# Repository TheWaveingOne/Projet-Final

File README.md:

# Projet-Final
 Projet synthèse pour mon DEC

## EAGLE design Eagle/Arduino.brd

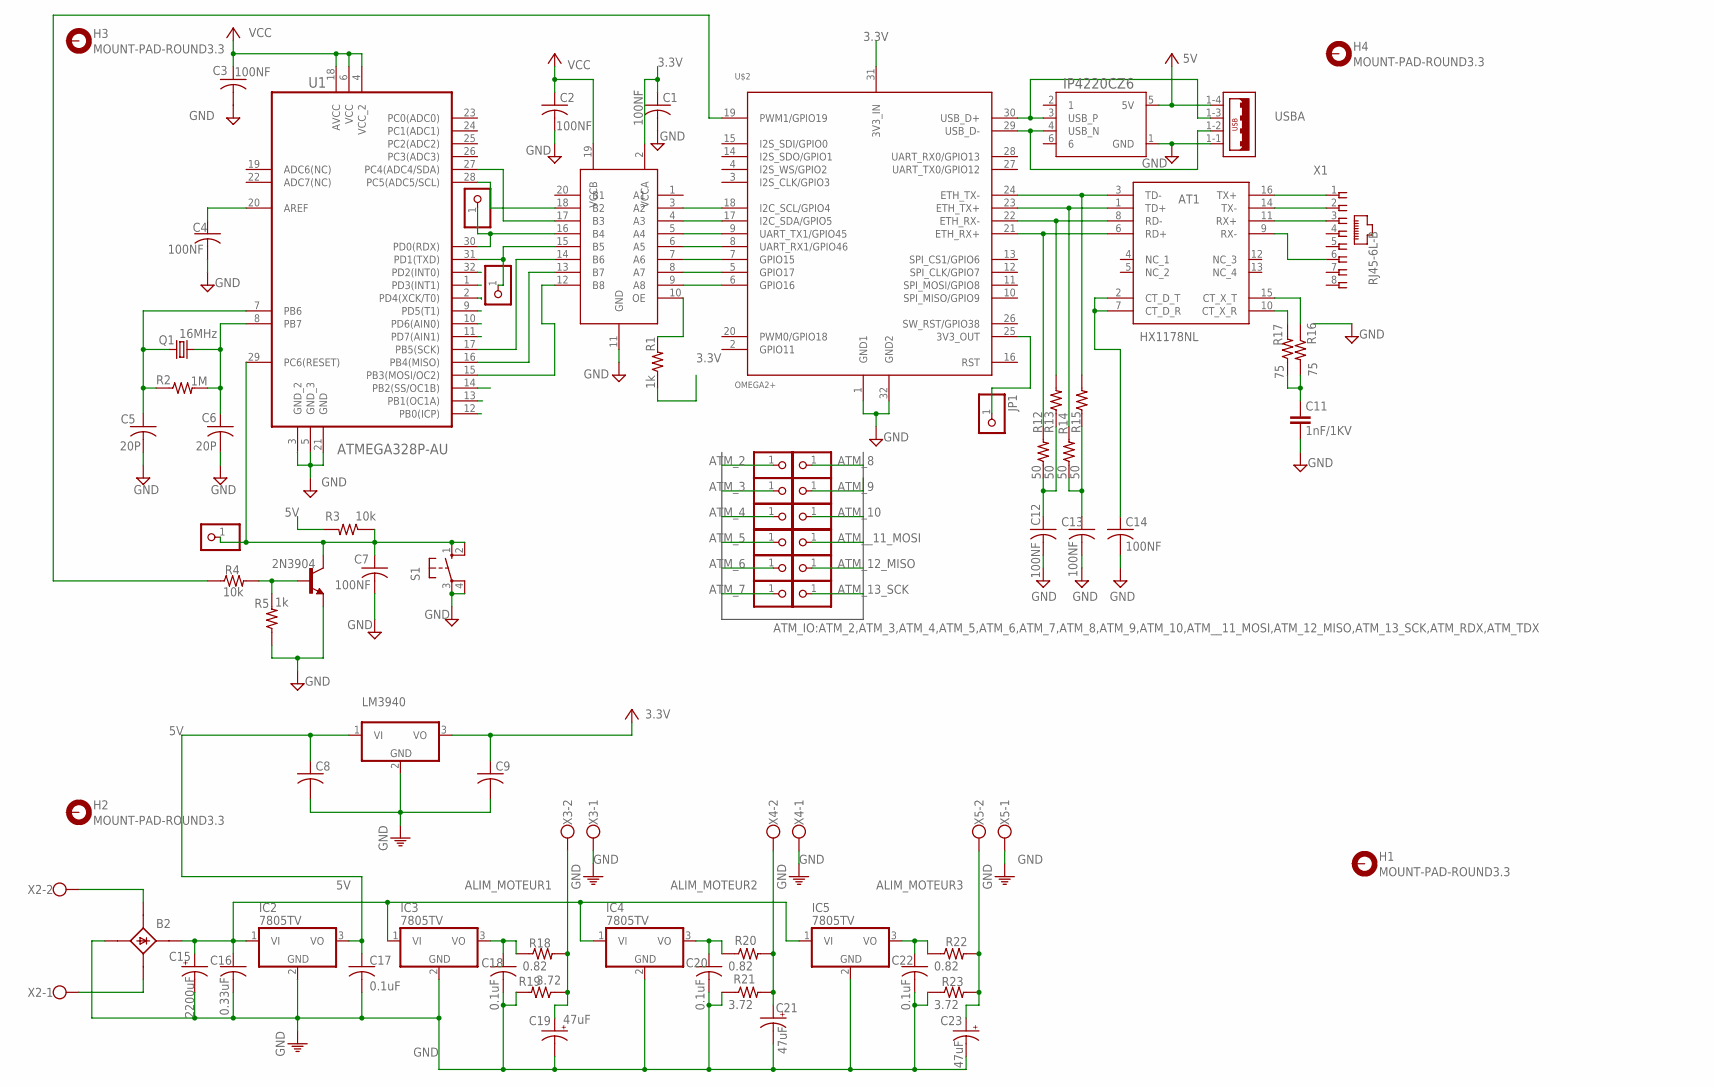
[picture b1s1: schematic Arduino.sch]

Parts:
AT1: HX1178NL; SOP254P1283X647-16N
B2: B25A-
C1, C2, C3, C4, C7, C12, C13, C14: 100NF; C0603K
C5, C6: 20P; C0603K
C8, C9: CENPC1206K; C1206K
C11: 1nF/1KV; XC10B6
C15: 2200uF; SANYO-OSCON_B'
C16: 0.33uF; C0603K
C17, C18, C20, C22: 0.1uF; C0603K
C19, C21, C23: 47uF; SANYO-OSCON_B'
FRAME1: CARTOUCHE_TGÉ; CARTOUCHE
H1, H2, H3, H4: MOUNT-PAD-ROUND3.3; 3,3-PAD
IC2, IC3, IC4, IC5: 7805TV; TO220V
IP4220CZ6: IP4220CZ6,125DIODE_SOT457_1P7X3P1-M; DIODE_SOT457_1P7X3P1-M
JP1, JP2, JP3, JP4, JP5, JP6, JP7, JP8, JP9, JP10, JP11, JP12, JP13, JP14, JP15, JP16: PINHD-1X1; 1X01
LM3940: 7824TV; TO220V
Q1: 16MHz; HC49/S
R1: 1k; M1206
R2: 1M; M1206
R3, R4: 10k; M1206
R5: 1k; M3216
R12, R13, R14, R15: 50; M1206
R16, R17: 75; M1206
R18, R20, R22: 0.82; 0309/10
R19, R21, R23: 3.72; 0309/10
S1: 10-XX; B3F-10XX
U1: ATMEGA328P-AU; QFP80P900X900X120-32N
U$1: TXS0108E; TSSOP20
U$2: OMEGA2+; OMEGA2_PADS
USB: USB_2P85-32003-00X-1; USB2
VERIFIER_TYPE: 2N3904; TO92
X1: RJ45-6L-B; RJ45-NO-SHIELD
X2, X3, X4, X5: W237-102

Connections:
3.3V: C1.1, C9.1, LM3940.3 (VO), R1.1, U$1.2 (VCCA), U$2.31 (3V3_IN)
5V: C2.1, C3.1, C8.1, C17.1, IC2.3 (VO), IP4220CZ6.5 (5V), LM3940.1 (VI), R3.2, U1.4 (VCC_2), U1.6 (VCC), U1.18 (AVCC), U$1.19 (VCCB), USB.1-4 (4)
ALIM_MOTEUR1: C19.+, R18.2, R19.1, X3.2
ALIM_MOTEUR2: C21.+, R20.2, R21.2, X4.2
ALIM_MOTEUR3: C23.+, R22.2, R23.2, X5.2
ATM_2: JP3.1, U1.32 (PD2(INT0))
ATM_3: JP4.1, U1.1 (PD3(INT1))
ATM_4: JP7.1, U1.2 (PD4(XCK/T0))
ATM_5: JP8.1, U1.9 (PD5(T1))
ATM_6: JP9.1, U1.10 (PD6(AIN0))
ATM_7: JP10.1, U1.11 (PD7(AIN1))
ATM_8: JP11.1, U1.12 (PB0(ICP))
ATM_9: JP12.1, U1.13 (PB1(OC1A))
ATM_10: JP13.1, U1.14 (PB2(SS/OC1B))
ATM_12_MISO: JP15.1, U1.16 (PB4(MISO)), U$1.13 (B7)
ATM_13_SCK: JP16.1, U1.17 (PB5(SCK)), U$1.14 (B6)
ATM_RDX: JP5.1, U1.30 (PD0(RDX)), U$1.16 (B4)
ATM_SCI: U1.28 (PC5(ADC5/SCL)), U$1.18 (B2)
ATM_SDA: U1.27 (PC4(ADC4/SDA)), U$1.17 (B3)
ATM_TDX: JP6.1, U1.31 (PD1(TXD)), U$1.15 (B5)
ATM__11_MOSI: JP14.1, U1.15 (PB3(MOSI/OC2)), U$1.12 (B8)
GND: B2.-1 (-), C1.2, C2.2, C3.2, C4.2, C5.2, C6.2, C7.2, C8.2, C9.2, C11.2, C12.2, C13.2, C14.2, C15.-, C16.2, C17.2, C18.2, C19.-, C20.2, C21.-, C22.2, C23.-, IC2.2 (GND), IC3.2 (GND), IC4.2 (GND), IC5.2 (GND), IP4220CZ6.1 (GND), LM3940.2 (GND), R5.1, R19.2, R21.1, R23.1, S1.3, S1.4 (P1), U1.3 (GND_2), U1.5 (GND_3), U1.21 (GND), U$1.11 (GND), U$2.1 (GND1), U$2.32 (GND2), USB.1-1 (1), VERIFIER_TYPE.3 (E), X3.1, X4.1, X5.1
MCU_RESET: C7.1, JP2.1, R3.1, S1.1 (S), S1.2 (S1), U1.29 (PC6(RESET)), VERIFIER_TYPE.1 (C)
unnamed: R1.2, U$1.10 (OE)
unnamed: C4.1, U1.20 (AREF)
unnamed: C6.1, Q1.2, R2.2, U1.8 (PB7)
unnamed: C5.1, Q1.1, R2.1, U1.7 (PB6)
unnamed: C11.1, R16.2, R17.1
unnamed: AT1.2 (CT_D_T), AT1.7 (CT_D_R), C14.1
unnamed: AT1.15 (CT_X_T), R16.1
unnamed: AT1.10 (CT_X_R), R17.2
unnamed: R4.1, U$2.19 (PWM1/GPIO19)
unnamed: B2.AC1- (AC1), X2.2
unnamed: B2.AC2- (AC2), X2.1
unnamed: C18.1, IC3.3 (VO), R18.1
unnamed: C20.1, IC4.3 (VO), R20.1
unnamed: C22.1, IC5.3 (VO), R22.1
unnamed: R4.2, R5.2, VERIFIER_TYPE.2 (B)
unnamed: IP4220CZ6.3 (USB_P), U$2.30 (USB_D+), USB.1-3 (3)
unnamed: IP4220CZ6.4 (USB_N), U$2.29 (USB_D-), USB.1-2 (2)
unnamed: AT1.3 (TD-), R15.2, U$2.24 (ETH_TX-)
unnamed: AT1.1 (TD+), R14.2, U$2.23 (ETH_TX+)
unnamed: AT1.8 (RD-), R13.2, U$2.22 (ETH_RX-)
unnamed: AT1.6 (RD+), R12.2, U$2.21 (ETH_RX+)
unnamed: AT1.16 (TX+), X1.1
unnamed: AT1.14 (TX-), X1.2
unnamed: AT1.11 (RX+), X1.3
unnamed: AT1.9 (RX-), X1.6
unnamed: C12.1, R12.1, R13.1
unnamed: C13.1, R14.1, R15.1
OM_IO15: U$1.7 (A6), U$2.7 (GPIO15)
OM_IO16: U$1.9 (A8), U$2.6 (GPIO16)
OM_IO17: U$1.8 (A7), U$2.5 (GPIO17)
OM_RXD1: U$1.6 (A5), U$2.8 (UART_RX1/GPIO46)
OM_SCI: U$1.3 (A2), U$2.18 (I2C_SCL/GPIO4)
OM_SDA: U$1.4 (A3), U$2.17 (I2C_SDA/GPIO5)
OM_TXD1: U$1.5 (A4), U$2.9 (UART_TX1/GPIO45)
TP_3.3_OMEGA: JP1.1, U$2.25 (3V3_OUT)
VIN_7805: B2.+1 (+), C15.+, C16.1, IC2.1 (VI), IC3.1 (VI), IC4.1 (VI), IC5.1 (VI)

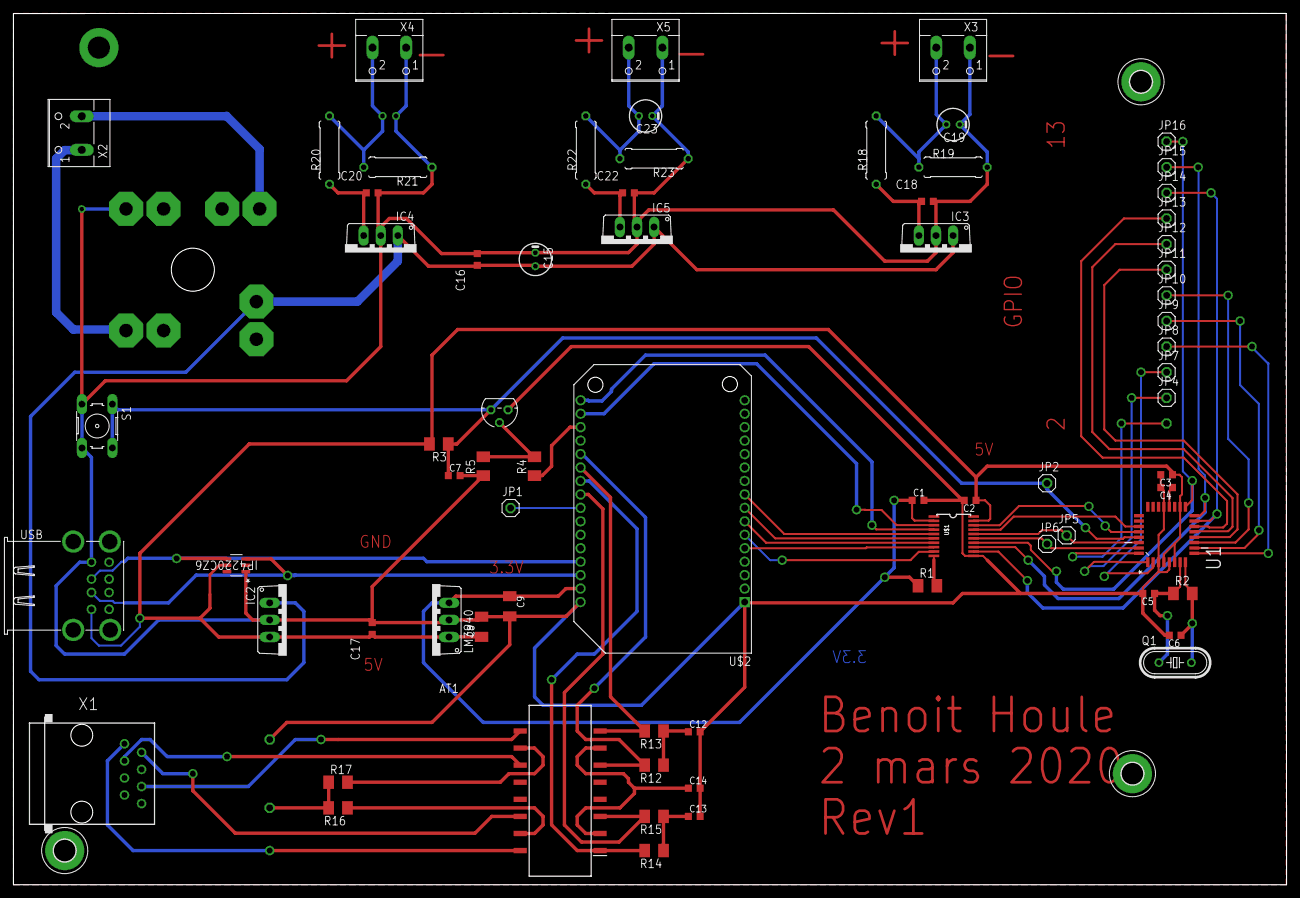
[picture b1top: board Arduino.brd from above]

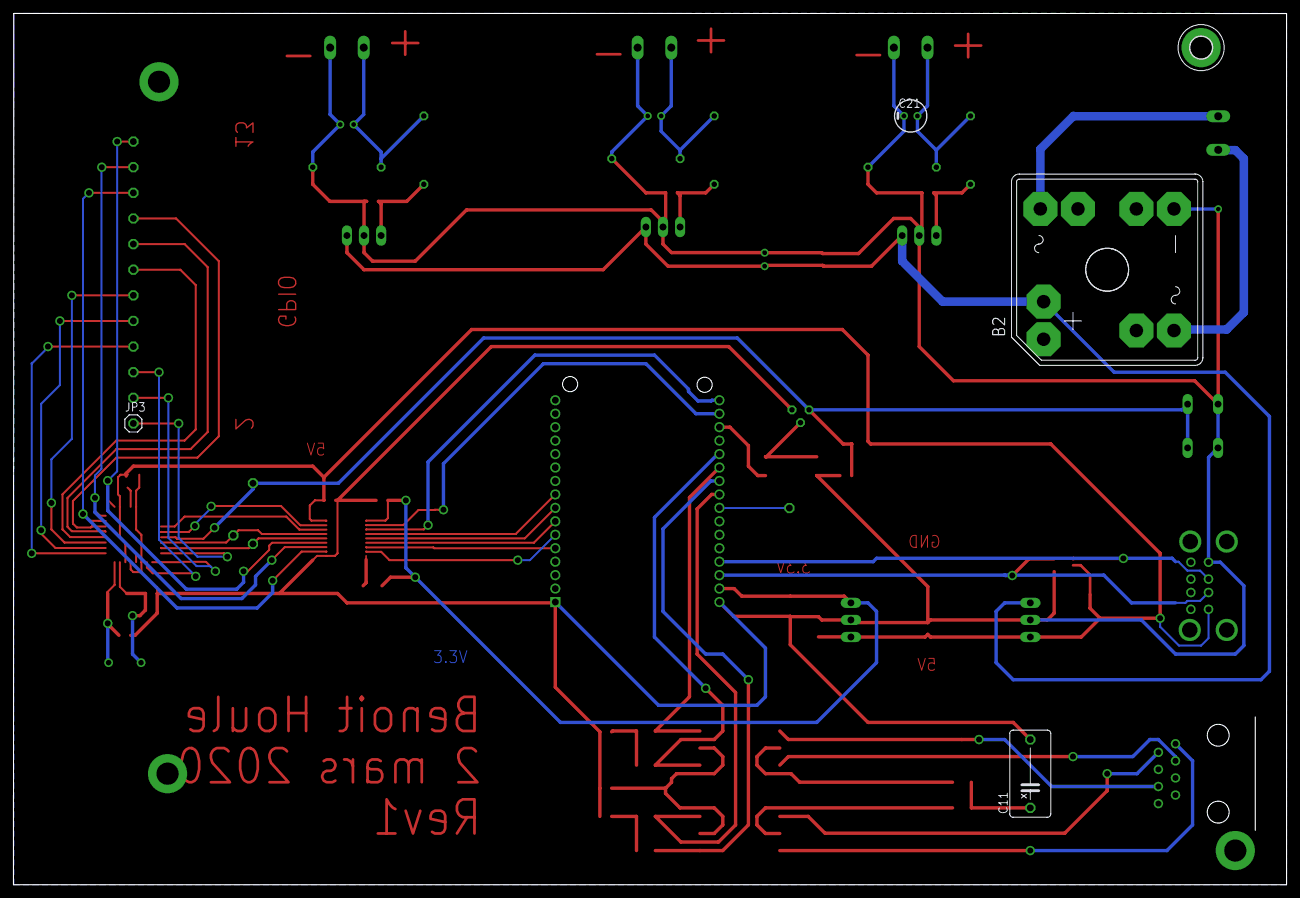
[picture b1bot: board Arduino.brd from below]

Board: 2 copper layers, 189.3 x 129.5 mm, 80 parts (5 on the bottom side), 59 nets.

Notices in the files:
parts and their libraries:
COPYRIGHT: Copyright (C) 2016 Accelerated Designs. All rights reserved
